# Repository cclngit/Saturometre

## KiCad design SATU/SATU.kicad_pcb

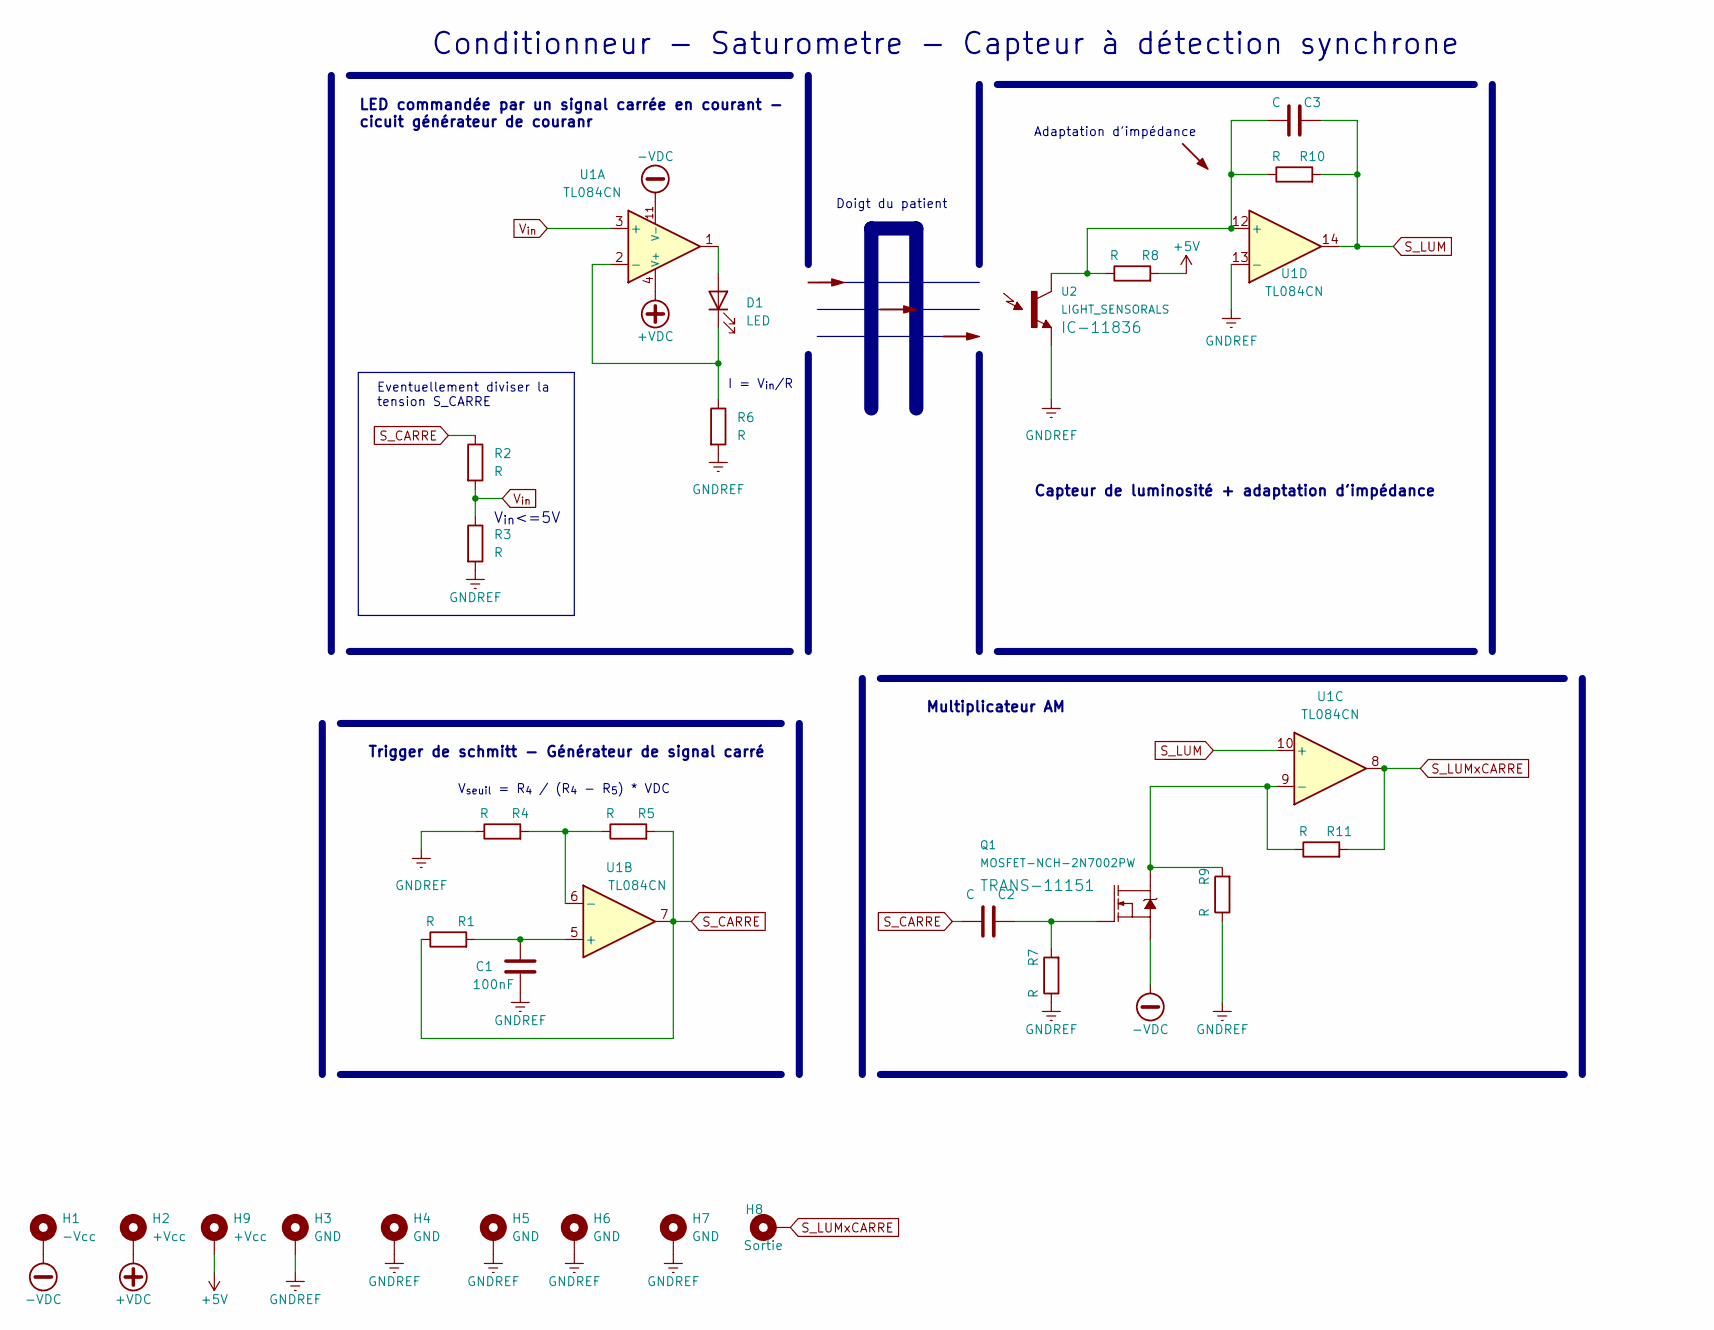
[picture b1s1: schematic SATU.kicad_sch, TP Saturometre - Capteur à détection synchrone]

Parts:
C1: 100nF; C_1812_4532Metric
C2: C; C_1812_4532Metric
C3: C; C_3640_9110Metric
D1: LED; LED_D8.0mm
H1: -Vcc; MountingHole_2.2mm_M2_Pad_TopBottom
H2, H9: +Vcc; MountingHole_2.2mm_M2_Pad_TopBottom
H3, H4, H5, H6, H7: GND; MountingHole_2.2mm_M2_Pad_TopBottom
H8: Sortie; MountingHole_2.2mm_M2_Pad_TopBottom
Q1: MOSFET-NCH-2N7002PW; SOT323
R1, R2, R3, R4, R5, R6, R7, R8, R9, R10, R11: R; R_2512_6332Metric
U1: TL084CN; DIP850W50P254L2000H510Q14N
U2: LIGHT_SENSORALS; LED_Rectangular_W3.9mm_H1.8mm

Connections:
+5V: H9.1, R8.2
+VDC: H2.1, U1.4 (V+)
-VDC: H1.1, Q1.2 (S), U1.11 (V-)
GNDREF: C1.2, H3.1, H4.1, H5.1, H6.1, H7.1, R3.2, R4.1, R6.2, R7.1, R9.1, U1.13 (-), U2.2 (E1)
unnamed: C1.1, R1.2, U1.5 (+)
unnamed: C2.1, Q1.1 (G), R7.2
unnamed: C3.2, R8.1, R10.1, U1.12 (+), U2.1 (C1)
unnamed: D1.1 (K), R6.1, U1.2 (-)
unnamed: D1.2 (A), U1.1
unnamed: Q1.3 (D), R9.2, R11.1, U1.9 (-)
unnamed: R4.2, R5.1, U1.6 (-)
S_CARRE: C2.2, R1.1, R2.1, R5.2, U1.7
S_LUM: C3.1, R10.2, U1.10 (+), U1.14
S_LUMxCARRE: H8.1, R11.2, U1.8
V_{in}: R2.2, R3.1, U1.3 (+)

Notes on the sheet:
Capteur de luminosité + adaptation d'impédance
Trigger de schmitt - Générateur de signal carré
Conditionneur - Saturometre - Capteur à détection synchrone
V_{in}<=5V
V_{seuil} = R_{4} / (R_{4} - R_{5}) * VDC
LED commandée par un signal carrée en courant - cicuit générateur de couranr
Multiplicateur AM
I = V_{in}/R
Adaptation d'impédance
Eventuellement diviser la tension S_CARRE
Doigt du patient

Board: 2 copper layers, 27 parts (0 on the bottom side), 15 nets, no tracks yet.

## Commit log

2023-03-09 init
